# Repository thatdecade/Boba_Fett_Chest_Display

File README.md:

# Boba-Fett-Chest-Display
This is the software and hardware design for the display on Boba Fett’s chest plate.  It was developed in collaboration with Joshua Kane.

The animation script is laid out in an easy to understand format.  Each segment of the display is fully programmable in the animation.
Just 12 lines of code to processes the animation and update the display!

Video Demo: https://www.flickr.com/photos/dwest2/23788341410

Video Build Guide: https://youtu.be/qv9qykpNFjM

Part List: https://www.mouser.com/ProjectManager/ProjectDetail.aspx?AccessID=554d07ab05

PCB Main Board: https://oshpark.com/shared_projects/f60TBgnX

PCB Bargraph Board: https://www.oshpark.com/shared_projects/E4qjCF4r

PCB Assembly Guide: http://www.westaby.net/2016/01/guide-boba-fett-chest-display/

Animation sequences for ESB, RTOJ, and Mandalorian are included.  For a customized sequence:
- Open the sequence_builder.xlsx or visit: https://www.westaby.net/7seg/
- There are three tabs, Seq Builder, Encoder, and Decoder.
- On the Seq Builder tab, enter 1s and 0s to light up the characters as you wish.
- Copy the indicated cell and paste the values to the sequence rows (right click, paste values)
- When finished, copy the finished sequence into the arduino code.
- Update CHAR_SEQUENCE_SIZE with the number of lines in your animation sequence
------------------------
# Boba-Fett-Chest-Display

This is the software and hardware design for the display on Boba Fett’s chest plate. It was developed in collaboration with Joshua Kane.

The animation script is laid out in an easy to understand format.  Each segment of the display is fully programmable in the animation.
Just 12 lines of code to processes the animation and update the display!

## Video Resources
- **Video Demo**: [Watch on Flickr](https://www.flickr.com/photos/dwest2/23788341410)
- **Video Build Guide**: [Watch on YouTube](https://youtu.be/qv9qykpNFjM)

## Hardware Resources
- **Part List**: [View on Mouser](https://www.mouser.com/ProjectManager/ProjectDetail.aspx?AccessID=554d07ab05)
- **PCB Main Board**: [View on OshPark](https://oshpark.com/shared_projects/f60TBgnX)
- **PCB Bargraph Board**: [View on OshPark](https://www.oshpark.com/shared_projects/E4qjCF4r)
- **PCB Assembly Guide**: [Read the Guide](http://www.westaby.net/2016/01/guide-boba-fett-chest-display/)

## Animation Sequences
Animation sequences for **ESB**, **ROTJ**, and **Mandalorian** are included. To create a customized sequence, follow these steps using the [7-Segment LED Display Animator Tool](https://www.westaby.net/7seg/):

1. **Open the Animator Tool**: [https://www.westaby.net/7seg/](https://www.westaby.net/7seg/) 

2. **Create Your Animation**:
   - Click on the segments of each digit to turn them on or off, creating your desired pattern.
   - Click the **"Save Frame"** button to record the current state of the display, adding it as a frame in your animation sequence.
   - Click the **"Playback Animation"** button to preview your animation on the display.
   - Once satisfied with your animation, click the **"Copy Code"** button to copy the animation data to your clipboard. This can be directly pasted into your Arduino code.

3. **Configure Arduino Code**:
   - In your Arduino sketch, paste the copied animation data where appropriate.
   - Update the `CHAR_SEQUENCE_SIZE` constant to match the number of frames in your animation sequence.

## Getting Started
1. **Assemble the Hardware**:
   - Follow the [PCB Assembly Guide](http://www.westaby.net/2016/01/guide-boba-fett-chest-display/) to assemble the main and bargraph PCBs.
   - Ensure all components are correctly placed and soldered.

2. **Upload the Firmware**:
   - Connect your assembled display to your computer via USB.
   - Open the Arduino IDE and load your sketch.  
   - Paste the animation data into your sketch and upload it to the microcontroller.

3. **Power Up**:
   - Once the firmware is uploaded, power the display to see your custom animations in action.

## License
[GNU General Public License v3.0](LICENSE)

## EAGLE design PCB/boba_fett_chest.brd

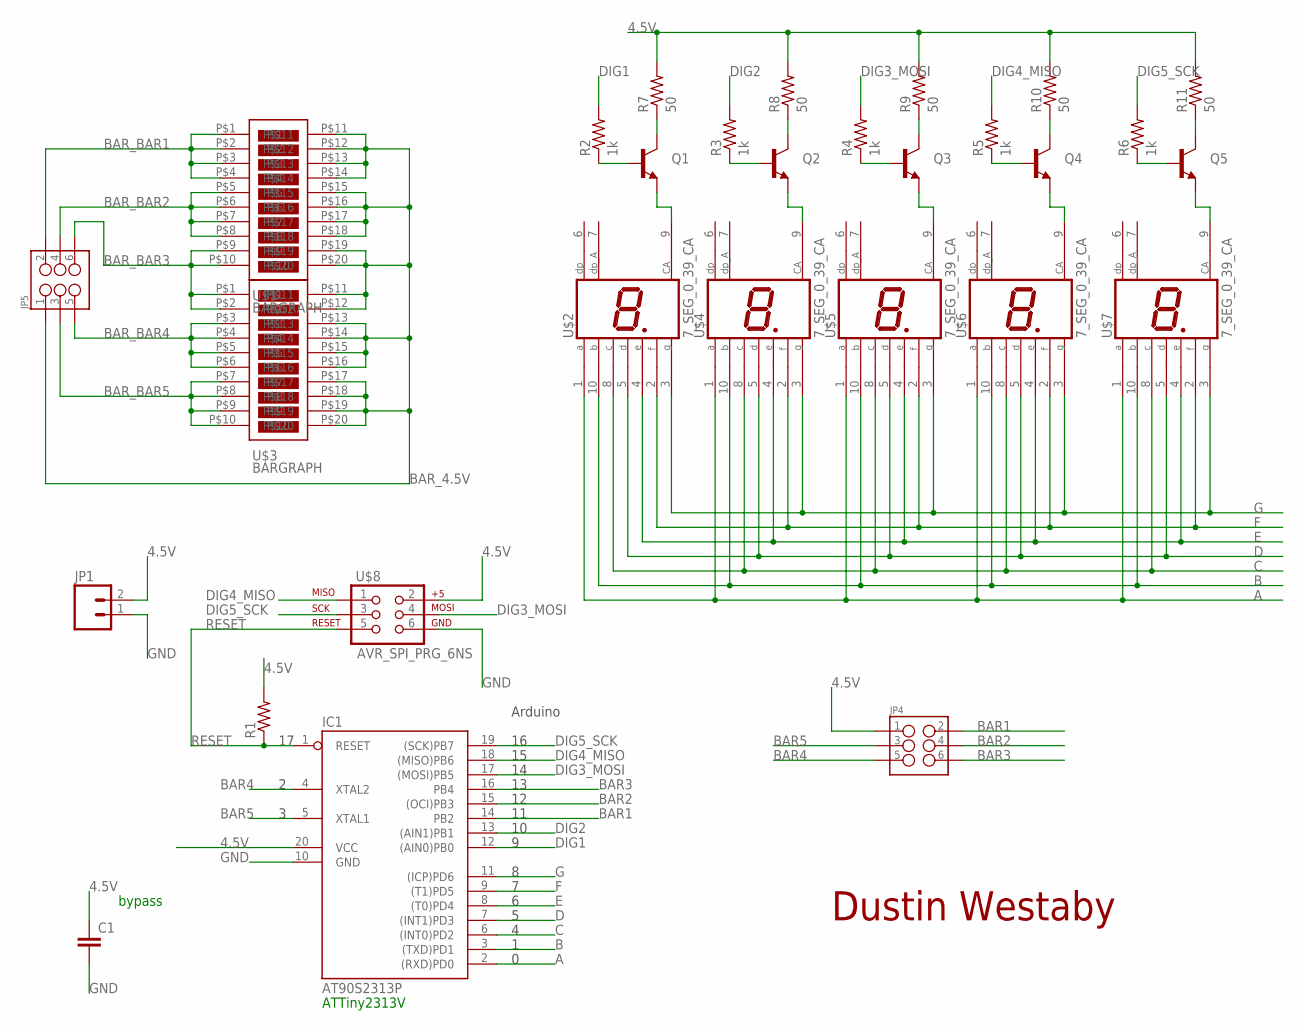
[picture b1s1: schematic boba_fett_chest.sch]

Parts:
C1: CAPCAP-PTH-2MM; CAP-PTH-2MM
IC1: AT90S2313P; DIL20
JP1: M02PTH; 1X02
JP4, JP5: M03X22X3_SILK_SM; 2X3
Q1, Q2, Q3, Q4, Q5: TRANSISTOR_NPNTO92; TO-92
R1: RESISTORPTH1; AXIAL-0.3
R2, R3, R4, R5, R6: 1k; AXIAL-0.3
R7, R8, R9, R10, R11: 50; AXIAL-0.3
U$1, U$3: BARGRAPH
U$2, U$4, U$5, U$6, U$7: 7_SEG_0_39_CA; 0_39_DISP
U$8: AVR_SPI_PRG_6NS; 2X3-NS

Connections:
4.5V: C1.1, IC1.20 (VCC), JP1.2, JP4.1, R1.P$2 (2), R7.P$2 (2), R8.P$2 (2), R9.P$2 (2), R10.P$2 (2), R11.P$2 (2), U$8.2
A: IC1.2 ((RXD)PD0), U$2.1 (A), U$4.1 (A), U$5.1 (A), U$6.1 (A), U$7.1 (A)
B: IC1.3 ((TXD)PD1), U$2.10 (B), U$4.10 (B), U$5.10 (B), U$6.10 (B), U$7.10 (B)
BAR1: IC1.14 (PB2), JP4.2
BAR2: IC1.15 ((OCI)PB3), JP4.4
BAR3: IC1.16 (PB4), JP4.6
BAR4: IC1.4 (XTAL2), JP4.5
BAR5: IC1.5 (XTAL1), JP4.3
BAR_4.5V: JP5.1, U$1.P$11, U$1.P$12, U$1.P$13, U$1.P$14, U$1.P$15, U$1.P$16, U$1.P$17, U$1.P$18, U$1.P$19, U$1.P$20, U$3.P$11, U$3.P$12, U$3.P$13, U$3.P$14, U$3.P$15, U$3.P$16, U$3.P$17, U$3.P$18, U$3.P$19, U$3.P$20
BAR_BAR1: JP5.2, U$1.P$1, U$1.P$2, U$1.P$3, U$1.P$4
BAR_BAR2: JP5.4, U$1.P$5, U$1.P$6, U$1.P$7, U$1.P$8
BAR_BAR3: JP5.6, U$1.P$9, U$1.P$10, U$3.P$1, U$3.P$2
BAR_BAR4: JP5.5, U$3.P$3, U$3.P$4, U$3.P$5, U$3.P$6
BAR_BAR5: JP5.3, U$3.P$7, U$3.P$8, U$3.P$9, U$3.P$10
C: IC1.6 ((INT0)PD2), U$2.8 (C), U$4.8 (C), U$5.8 (C), U$6.8 (C), U$7.8 (C)
D: IC1.7 ((INT1)PD3), U$2.5 (D), U$4.5 (D), U$5.5 (D), U$6.5 (D), U$7.5 (D)
DIG1: IC1.12 ((AIN0)PB0), R2.P$2 (2)
DIG2: IC1.13 ((AIN1)PB1), R3.P$2 (2)
DIG3_MOSI: IC1.17 ((MOSI)PB5), R4.P$2 (2), U$8.4
DIG4_MISO: IC1.18 ((MISO)PB6), R5.P$2 (2), U$8.1
DIG5_SCK: IC1.19 ((SCK)PB7), R6.P$2 (2), U$8.3
E: IC1.8 ((T0)PD4), U$2.4 (E), U$4.4 (E), U$5.4 (E), U$6.4 (E), U$7.4 (E)
F: IC1.9 ((T1)PD5), U$2.2 (F), U$4.2 (F), U$5.2 (F), U$6.2 (F), U$7.2 (F)
G: IC1.11 ((ICP)PD6), U$2.3 (G), U$4.3 (G), U$5.3 (G), U$6.3 (G), U$7.3 (G)
GND: C1.2, IC1.10 (GND), JP1.1, U$8.6
unnamed: Q5.1 (E), U$7.9 (CA)
unnamed: Q4.1 (E), U$6.9 (CA)
unnamed: Q3.1 (E), U$5.9 (CA)
unnamed: Q2.1 (E), U$4.9 (CA)
unnamed: Q1.1 (E), U$2.9 (CA)
unnamed: Q1.2 (B), R2.P$1 (1)
unnamed: Q2.2 (B), R3.P$1 (1)
unnamed: Q3.2 (B), R4.P$1 (1)
unnamed: Q4.2 (B), R5.P$1 (1)
unnamed: Q5.2 (B), R6.P$1 (1)
unnamed: Q1.3 (C), R7.P$1 (1)
unnamed: Q2.3 (C), R8.P$1 (1)
unnamed: Q3.3 (C), R9.P$1 (1)
unnamed: Q4.3 (C), R10.P$1 (1)
unnamed: Q5.3 (C), R11.P$1 (1)
RESET: IC1.1 (RESET), R1.P$1 (1), U$8.5

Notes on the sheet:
bypass
ATTiny2313V
Arduino
Dustin Westaby

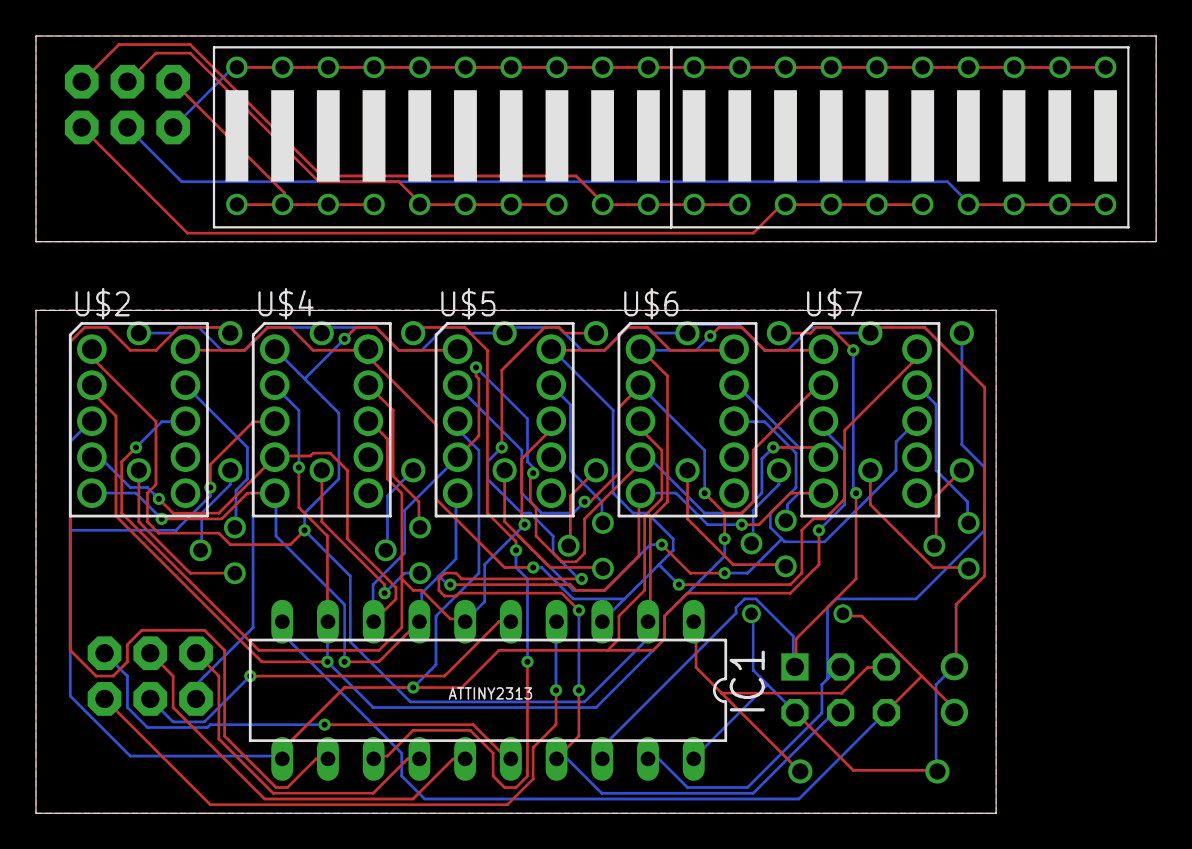
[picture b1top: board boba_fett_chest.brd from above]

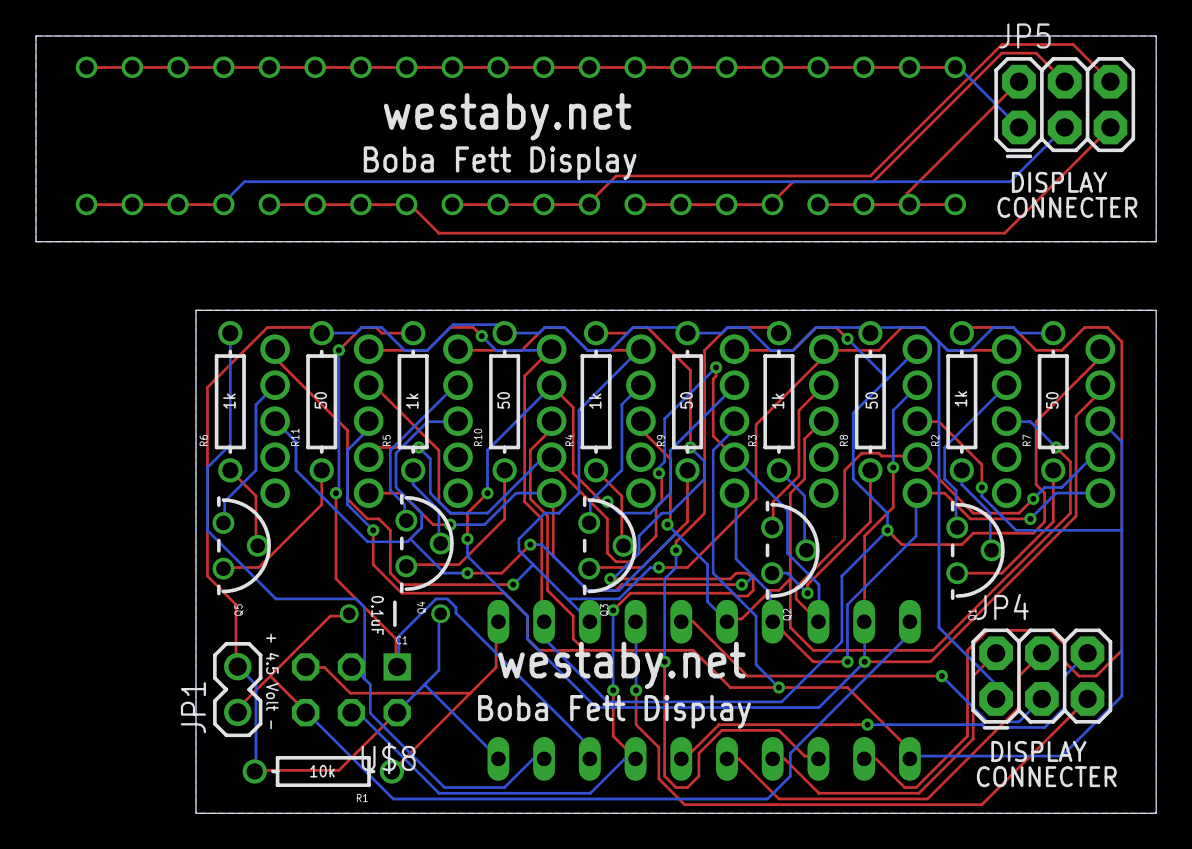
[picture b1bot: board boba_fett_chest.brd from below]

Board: 2 copper layers, 53.3 x 27.9 mm, 29 parts (21 on the bottom side), 41 nets.

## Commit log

2020-12-15 Sequence builder excel file
    Prepping for a mandalorian style animation
2021-01-03 Mandalorian sequence added.
    Reworked animation routines to allow the bargraph to be run async from the character animation.
2021-01-03 Added mandalorian animation.
    Reworked animation routines to allow the bargraph to be run async from the character animation.
2021-01-04 Linked mandalorian video demo
2021-01-27 Added compatibility for common cathode display types.
2021-02-24 Updated parts list link
2025-01-30 Added website usage
2025-01-30 Web Sequence Builder

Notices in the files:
parts and their libraries:
SparkFun-Connectors: Licensing: CC v3.0 Share-Alike You are welcome to use this library for commercial purposes.
